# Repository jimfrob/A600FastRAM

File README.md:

# A600FastRAM
A600FastRAM is an Open Hardware 4 MB Fast RAM Expansion for the Commodore Amiga 600 Computer. It is an almost complete copy of SukkoPera's OpenAmiga600FastRamExpansion. All that has been altered is the PCB design. This is because that design sticks out over Denise and would not fit with my RGB2HDMI. I have designed this board to fit around the Kickstart chip. I also used the Freerouting plugin in Kicad 7.0 as I find I'm not that good at routing traces manually.

VERY IMPORTANT WARNING: I haven't had any boards fabricated just yet, so I'm not sure of 1) whether it will actually fit, or 2) that it can be programmed in situ by just getting power from the 5V line of the CPU. I may find it necessary to put C13 from the original design back into mine so that an external power souce can be used.

### Summary
Most of the below text is a direct copy from SukkoPera's readme. I have altered it wherever it refers to decisions he made, actions he took, or items that have been removed from my board design.

Most low-end Amiga models only came with *Chip RAM*. "Big Box" models allowed for a different type of memory to be installed, known as *Fast RAM*, where *fast* means that it's dedicated to the main processor, so that it doesn't have to compete with the other chips in order to gain access to it (as is the case with Chip RAM). While both Chip and Fast RAM are limited in size, you can have at least a few MB of the latter on all Amigas (usually up to 8), while the former can never exceed 2 MB.

A600FastRAM will allow you to add 4 MB of Fast RAM to your Amiga 600. This way you will be able to run more applications at once and more quickly. If you combine it with a chip RAM expansion, you will also be able to run almost all games supported by WHDLoad, pushing the smallest of the Amigas to its limits. The Fast RAM will be mapped to `$200000-$5fffff`, which means it will not interfere with the PCMCIA address space.

Note that the A600 was not originally designed to support a Fast RAM expansion, which means Commodore didn't provide any connector for it. In theory it could be sandwiched between the CPU and mainboard, as usually done on A500s, but in the A600 the CPU is soldered directly to the mainboard and cannot be removed. Thus the only way to install it is to clip it over the CPU, using a PLCC socket placed upside-down. PLCC sockets are not meant to be used this way, so this is really a bit of a hack and might not even work in all cases. Space around the CPU is quite limited, hence the odd shape of this board.

A600FastRAM is basically a clone of [SukkoPera's OpenAmiga600FastRamExpansion](https://github.com/SukkoPera/OpenAmiga600FastRamExpansion) which is itself basically a clone of [a RAM expansion produced by Kipper2K a few years ago](http://eab.abime.net/showthread.php?t=64218), based on [an earlier design by lvd/NedoPC](http://lvd.nedopc.com/Projects/a600_8mb/index.html).

### Memory Compatibility
The required RAM Type is 16 Mbit (1M×16) DRAM in the SOJ-42 package with up to 70-80 ns access time. It is 5v-only DRAM (not SDRAM!) often found in old 72-pin SIMMs, EDO chips might work or not. All chips having *8160* in their part number should be OK.

See [OpenAmiga500FastRamExpansion](https://github.com/SukkoPera/OpenAmiga500FastRamExpansion#memory-compatibility) for a compatibility list.

### Assembly and Installation
Open your A600, doing your best not to crack any of the small tabs that hold the case together. If your A600 has the top part of the shielding, remove it and store it somewhere, as you will not be able to put it back in place when the expansion is installed. The same goes for the HD cradle, sorry.

Lots of A600s (and of A1200s, for the record) have issues with leaking electrolytic capacitors, therefore I really recommend to inspect them first, while you have your Amiga open. They might be leaking even if your Amiga shows no problems and when it finally will, it might be too late (= expensive) to salvage it. So, if you notice any white or brownish marks around those shiny metal cylinders, get them replaced. It is NOT an easy thing to do and you need some decent tools anyway, so I really recommend to contact a professional, there are many people on Amiga forums offering this kind of service.

I suggest soldering the RAM chips first: these can either be soldered directly to the board or installed in sockets. While soldering the chips might not be trivial for the unexperienced, sockets for the SOJ-42 package are hard to find and not really easier to solder either, so the choice is up to you.

Next you should solder all the remaining surface mount components, first on the top side and then on the bottom side. Keep the CPLD and CPU socket last.

Before soldering the CPU socket you will need to rework it a bit if you want a really good fit: get some sandpaper and follow [these instructions](SocketRework.md). After it has been soldered, you can cut the bottom of it so that the window in the PCB continues through the socket. Most sockets will already have holes on the bottom that will make this operation easier. This will allow you to install a 14x14mm heatsink on the CPU, which might be a good idea since placing this board over the CPU will somewhat reduce the heat dissipation capabilities of the chip. Make sure to use good thermal adhesive/glue, otherwise you risk to make the dissipation even worse.

When you are done with the soldering you will need to program the CPLD. Whenever you do so, **make sure to carefully remove the board from your Amiga, or you might risk damaging it**. You can find the firmware [here](https://github.com/SukkoPera/OpenAmiga500FastRamExpansion/tree/master/firmware), along with instructions on how to flash it. Make sure you use the 4 MB version! My design intends to use the 5V line from the CPU to power the board even for programming, but I am unsure whether this is a good idea. It works well enough for flashing the FPGA on the Icedrake accelerator in my A1200.

You are finally ready to install the expansion in your A600 but, before you do this, I suggest to clean the CPU pins using contact cleaner or isopropyl alcool and a toothbrush or cotton swabs, as all sorts of gunk will have probably gathered on them over the years. Let them dry well, then place the expansion over the CPU with the correct orientation and push it down firmly until it feels solidly in place. There should be no need to use the Force&trade;.

Before reassembling your case, I recommend to run [SysTest/Amiga Test Kit](https://github.com/keirf/Amiga-Stuff). Use the Memory option (<kbd>F1</kbd>), it must show 4 MB of Fast RAM. Then start the Memory Test (<kbd>F1</kbd> again) and let it run for 50-100 rounds: if it doesn't find any errors, you are probably good to go. If you get any errors, power off your computer and try to give the expansion a better fit, by pushing it further down or slightly twisting it back and forth.

It might happen that the board slowly works its way out of the socket over time. To avoid this you can anchor it to the mainboard using the hole to the left of the CPU, which should align with one of the holes for the HD cradle legs. If you have a 3D printer, another option is using [this nice frame designed by blekihun](https://www.thingiverse.com/thing:4824656).

Note that, as already mentioned, PLCC sockets are not meant to be used this way, which means that the contact quality degrades a bit with every insertion or removal of the board. So, try not to remove it unnecessarily. If you find that the contact has degraded so much that the machine is no longer stable, replace the socket with a new one.

### License
The OpenAmiga600FastRamExpansion documentation, including the design itself, is copyright &copy; SukkoPera 2019.

OpenAmiga600FastRamExpansion is Open Hardware licensed under the [CERN OHL v. 1.2](http://ohwr.org/cernohl).

You may redistribute and modify this documentation under the terms of the CERN OHL v.1.2. This documentation is distributed *as is* and WITHOUT ANY EXPRESS OR IMPLIED WARRANTIES whatsoever with respect to its functionality, operability or use, including, without limitation, any implied warranties OF MERCHANTABILITY, SATISFACTORY QUALITY, FITNESS FOR A PARTICULAR PURPOSE or infringement. We expressly disclaim any liability whatsoever for any direct, indirect, consequential, incidental or special damages, including, without limitation, lost revenues, lost profits, losses resulting from business interruption or loss of data, regardless of the form of action or legal theory under which the liability may be asserted, even if advised of the possibility or likelihood of such damages.

A copy of the full license is included in file [LICENSE.pdf](LICENSE.pdf), please refer to it for applicable conditions. In order to properly deal with its terms, please see file [LICENSE_HOWTO.pdf](LICENSE_HOWTO.pdf).

The contact points for information about manufactured Products (see section 4.2) are listed in file [PRODUCT.md](PRODUCT.md).

Any modifications made by Licensees (see section 3.4.b) shall be recorded in file [CHANGES.md](CHANGES.md).

The Documentation Location of the original project is https://github.com/SukkoPera/OpenAmiga600FastRamExpansion/.

### Support the Project
Since the project is open you are free to get the PCBs made by your preferred manufacturer, however in case you want to support the development, you can order them from PCBWay through this link:

### Thanks
- SukkoPera for his easy-to-modify design
- lvd for the initial design
- Kipper2K for making his boards
- majinga for helping with the testing

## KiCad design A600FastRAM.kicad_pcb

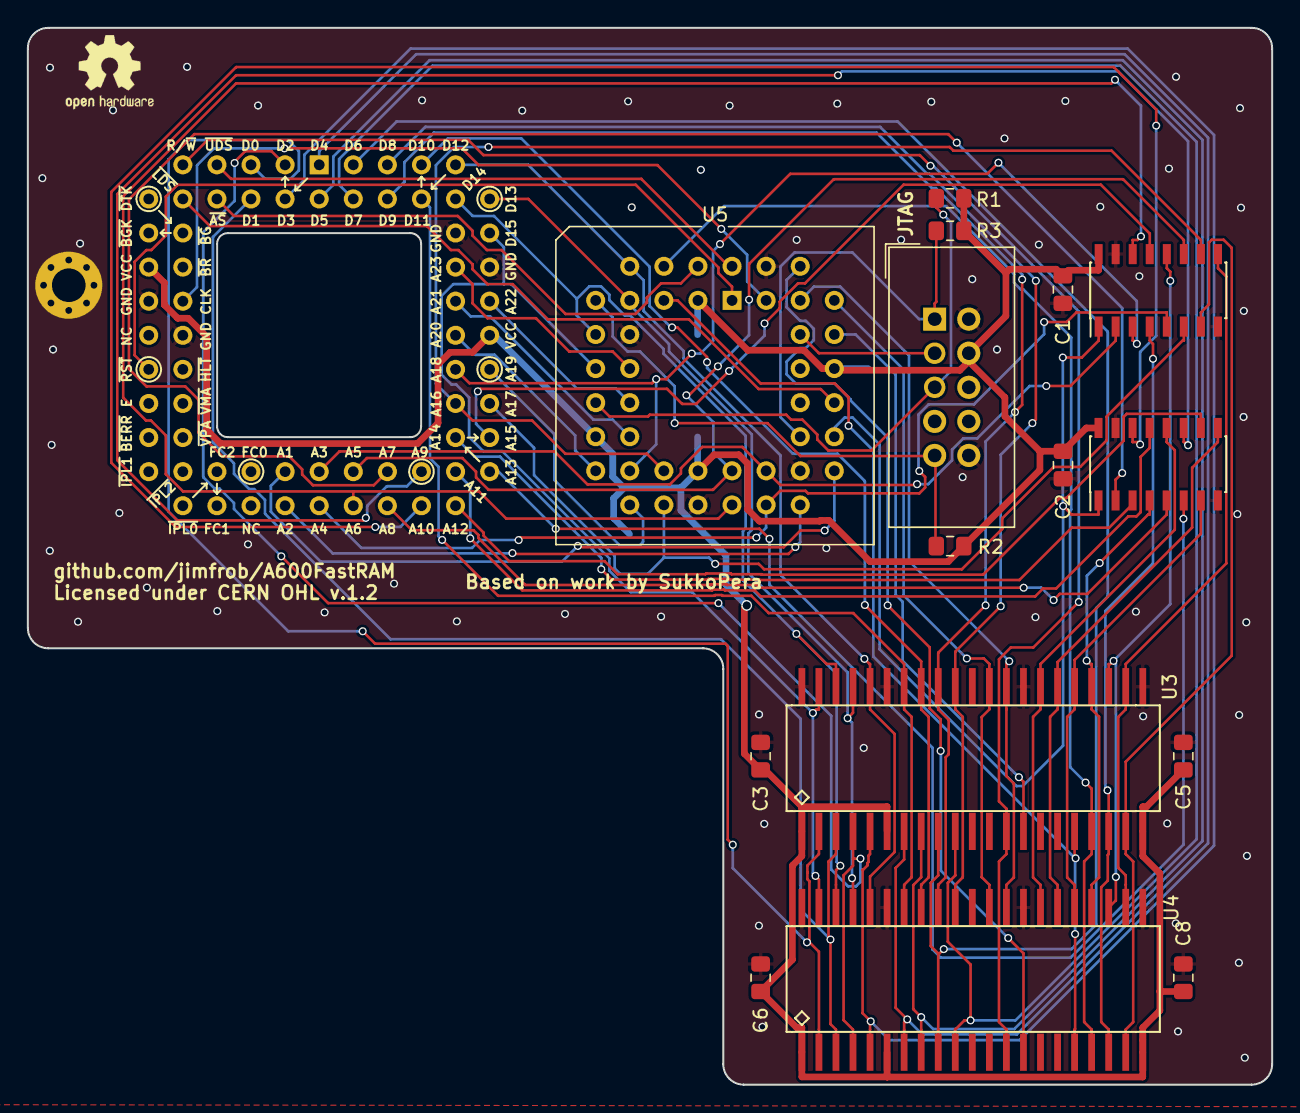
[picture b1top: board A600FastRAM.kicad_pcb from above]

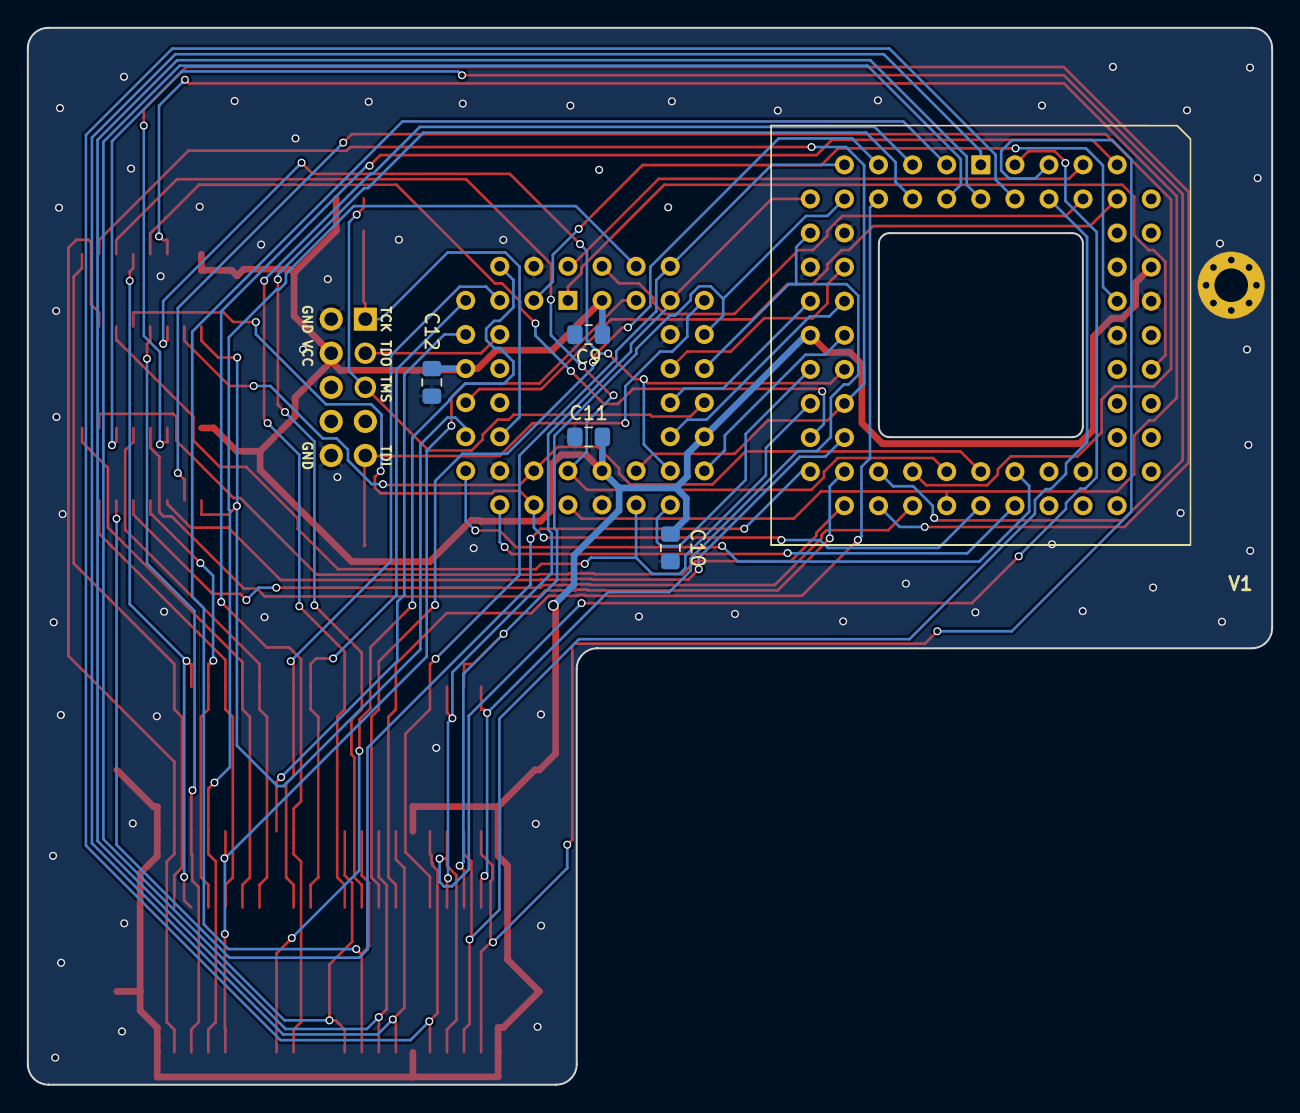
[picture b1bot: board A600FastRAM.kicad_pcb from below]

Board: 2 copper layers, 92.7 x 78.7 mm, 22 parts (4 on the bottom side), 66 nets.

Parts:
C1, C2, C3, C5, C6, C8, C9, C10, C11, C12: 100n; C_0805_2012Metric_Pad1.15x1.40mm_HandSolder
J1: MC68000_PLCC68; PLCC-68_THT-SocketUpsideDown
P1: JTAG_CONNECTOR; IDC-Header_2x05_P2.54mm_Vertical
P98: SCREW_HOLE; MountingHole_2.5mm_Pad_Via
P99: OSHW_LOGO; OSHW-Logo2_7.3x6mm_SilkScreen
R1, R2, R3: 10k; R_0805_2012Metric_Pad1.15x1.40mm_HandSolder
U1, U2: 74LS157; SOIC-16_3.9x9.9mm_P1.27mm
U3, U4: HYB5118160BSJ; SOJ-42-LongPads
U5: ATF1502AS-10JU44; PLCC-44_THT-Socket

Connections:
/a1: J1.32, U5.29
/a2: J1.33, U5.28
/a3: J1.34, U2.2, U5.27
/a4: J1.35, U2.5, U5.26
/a5: J1.36, U2.11, U5.25
/a6: J1.37, U2.14, U5.24
/a7: J1.38, U1.2
/a8: J1.39, U1.5
/a9: J1.40, U1.11
/a10: J1.41, U1.14
/a11: J1.42, U1.13
/a12: J1.43, U1.10
/a13: J1.44, U1.6
/a14: J1.45, U1.3
/a15: J1.46, U2.13
/a16: J1.47, U2.10, U5.21
/a17: J1.48, U2.6, U5.20
/a18: J1.49, U2.3, U5.19
/a19: J1.50, U5.18
/a20: J1.51, U5.17
/a21: J1.53, U5.16
/a22: J1.54, U5.14
/a23: J1.55, U5.12
/clk: J1.15, U5.43
/d0: J1.5, U3.2, U4.2
/d1: J1.4, U3.3, U4.3
/d2: J1.3, U3.4, U4.4
/d3: J1.2, U3.5, U4.5
/d4: J1.1, U3.7, U4.7
/d5: J1.68, U3.8, U4.8
/d6: J1.67, U3.9, U4.9
/d7: J1.66, U3.10, U4.10
/d8: J1.65, U3.33, U4.33
/d9: J1.64, U3.34, U4.34
/d10: J1.63, U3.35, U4.35
/d11: J1.62, U3.36, U4.36
/d12: J1.61, U3.38, U4.38, U5.6
/d13: J1.60, U3.39, U4.39, U5.8
/d14: J1.59, U3.40, U4.40, U5.9
/d15: J1.58, U3.41, U4.41, U5.11
/jtag_tck: P1.1, R3.2, U5.32
/jtag_tdi: P1.9, R2.2, U5.7
/jtag_tdo: P1.3, U5.38
/jtag_tms: P1.5, R1.2, U5.13
/ma0: U3.17, U4.17, U5.5
/ma1: U3.18, U4.18, U5.4
/ma2: U2.4, U3.19, U4.19
/ma3: U2.7, U3.20, U4.20
/ma4: U2.9, U3.23, U4.23
/ma5: U2.12, U3.24, U4.24
/ma6: U1.4, U3.25, U4.25
/ma7: U1.7, U3.26, U4.26
/ma8: U1.9, U3.27, U4.27
/ma9: U1.12, U3.28, U4.28
/mux_switch: U1.1, U2.1, U5.31
/r~w: J1.9, U3.13, U4.13
/~as: J1.6, U5.2
/~lcas: U3.31, U4.31, U5.39
/~lds: J1.8, U5.33
/~ras2: U3.14, U5.37
/~ras3: U4.14, U5.40
/~reset: J1.20, U5.1
/~ucas: U3.30, U4.30, U5.41
/~uds: J1.7, U5.44
GND: C1.2, C2.2, C3.2, C5.2, C6.2, C8.2, C9.2, C10.2, C11.2, C12.2, J1.16, J1.17, J1.56, J1.57, P1.2, P1.10, P98.1, U1.8, U1.15, U2.8, U2.15, U3.22, U3.29, U3.37, U3.42, U4.22, U4.29, U4.37, U4.42, U5.10, U5.22, U5.30, U5.42
VCC: C1.1, C2.1, C3.1, C5.1, C6.1, C8.1, C9.1, C10.1, C11.1, C12.1, J1.14, J1.52, P1.4, R1.1, R2.1, R3.1, U1.16, U2.16, U3.1, U3.6, U3.21, U4.1, U4.6, U4.21, U5.3, U5.15, U5.23, U5.35

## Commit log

2024-02-23 Update README.md
    partial update - pausing to add gerber renders
2024-02-23 Added gerber renders
2024-02-23 Update README.md
    Finished with first revision of the readme
2024-02-23 Update README.md
    wrong render chosen
2024-02-23 Made slight changes to board layout
2024-02-23 rounded the corners of the PCB
2024-02-26 Moved Open Hardware logo to silkscreen
    Additionally, the PCB is now a KiCAD 8.0 file
2024-02-26 Updated project files to KiCAD 8.0

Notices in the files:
A600FastRAM.kicad_pcb:
Licensed under CERN OHL v.1.2
